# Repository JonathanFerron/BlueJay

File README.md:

# BlueJay
 Split Ergonomic Keyboard

This is a project for a new split ergonomic QMK-powered keyboard. The goal is for it to be minimalist, meant for users who strictly touch-type, and made with easy to solder through-hole components. It is significantly inspired on the [Torn](https://github.com/rtitmuss/torn) split keyboard, with modifications such as adding a partial "numrow" and moving the thumb cluster further out.

This work is licensed under a
[Creative Commons Attribution-NonCommercial-ShareAlike 4.0 International License][cc-by-nc-sa].

[![CC BY-NC-SA 4.0][cc-by-nc-sa-image]][cc-by-nc-sa]

[cc-by-nc-sa]: http://creativecommons.org/licenses/by-nc-sa/4.0/
[cc-by-nc-sa-image]: https://licensebuttons.net/l/by-nc-sa/4.0/88x31.png
[cc-by-nc-sa-shield]: https://img.shields.io/badge/License-CC%20BY--NC--SA%204.0-lightgrey.svg

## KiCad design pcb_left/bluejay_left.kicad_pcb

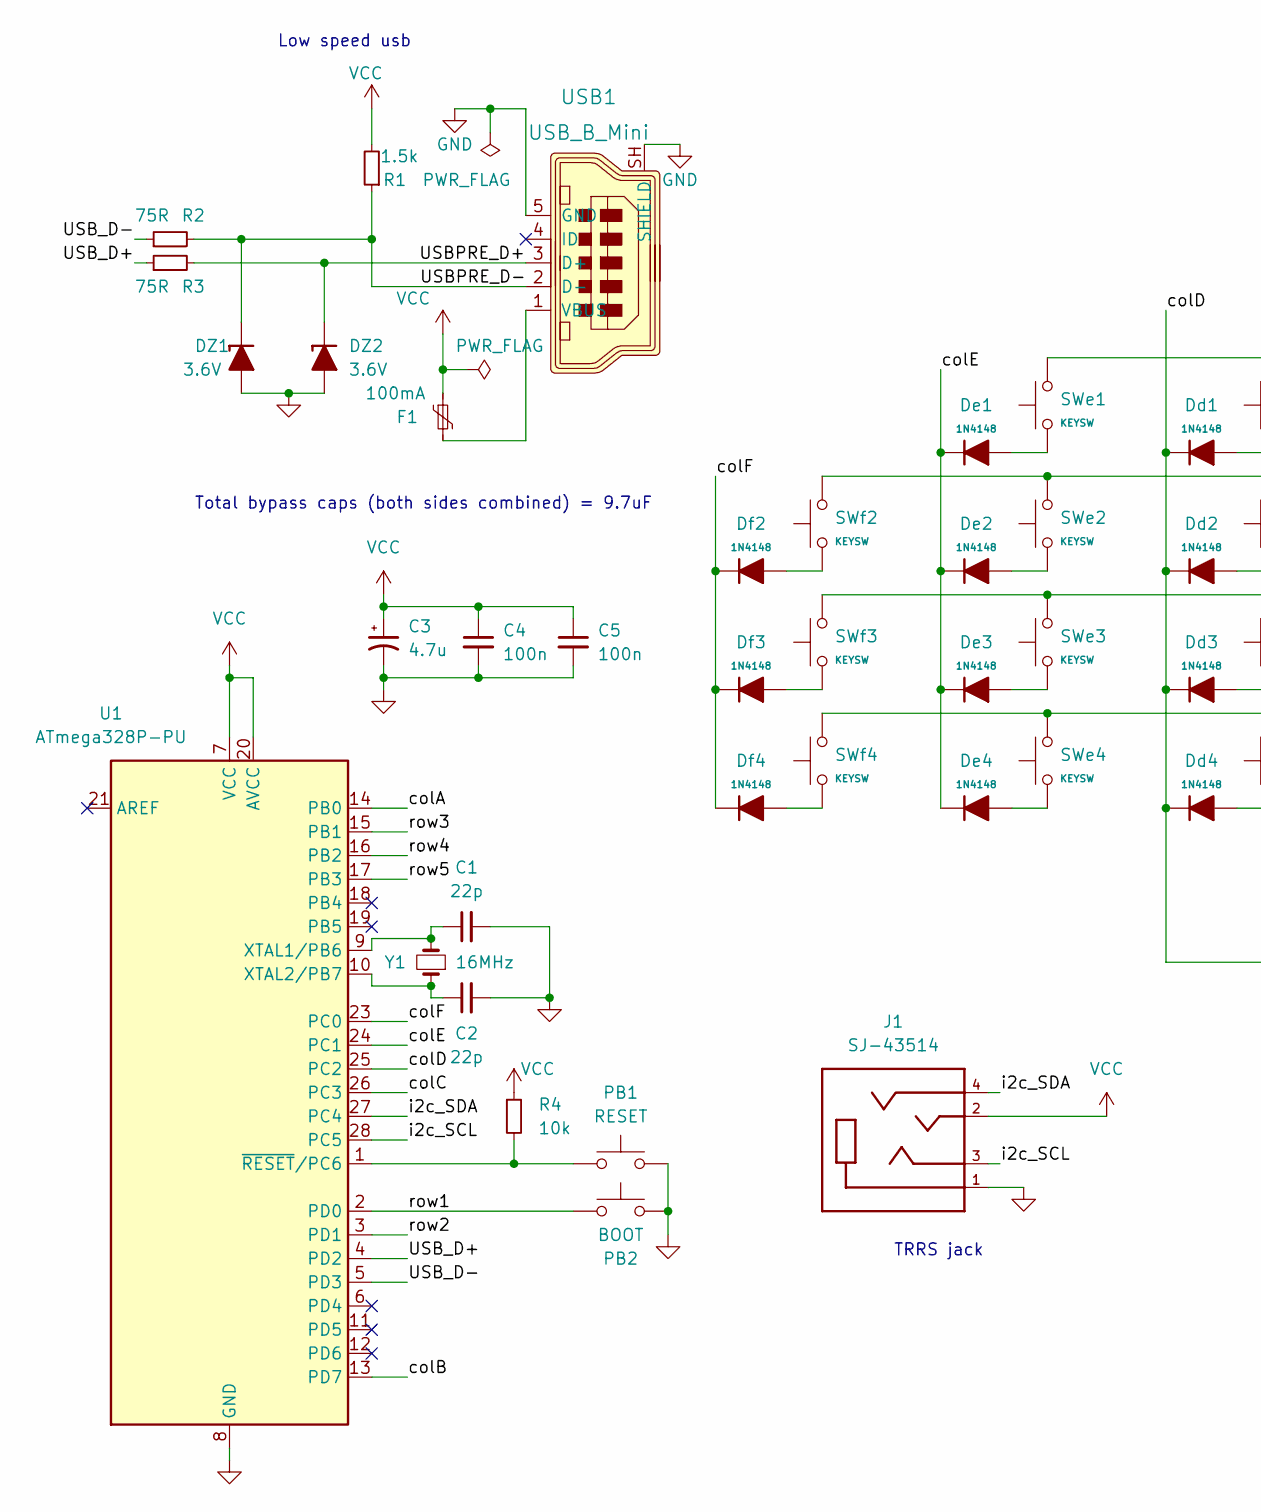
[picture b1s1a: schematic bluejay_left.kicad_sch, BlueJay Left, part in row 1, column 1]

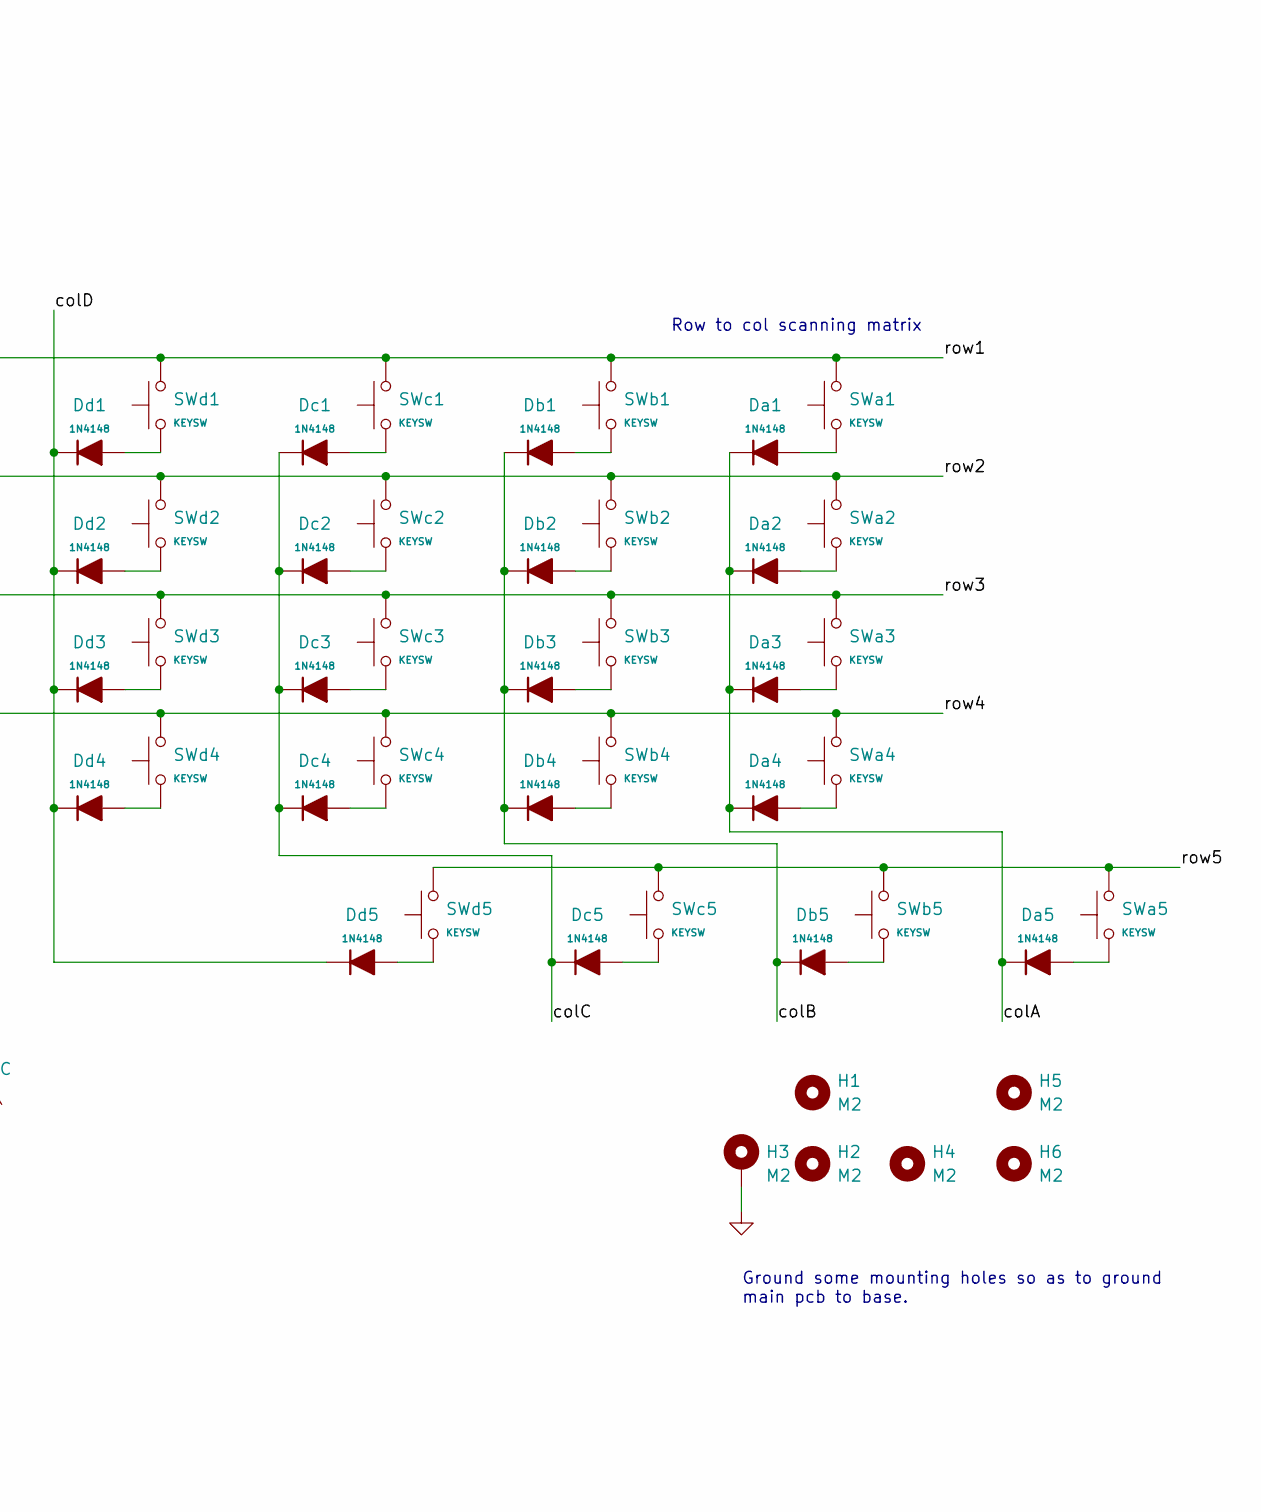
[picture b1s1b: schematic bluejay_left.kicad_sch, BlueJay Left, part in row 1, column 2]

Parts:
C1, C2: 22p; C_Disc_D3.0mm_W1.6mm_P2.50mm
C3: 4.7u; CP_Radial_D4.0mm_P1.50mm
C4, C5: 100n; C_Disc_D4.3mm_W1.9mm_P5.00mm
DZ1, DZ2: 3.6V; D_DO-35_SOD27_P5.08mm_Horizontal
Da1, Da2, Da3, Da4, Da5: 1N4148; D_DO-35_SOD27_P5.08mm_Horizontal
Db1, Db2, Db3, Db4, Db5: 1N4148; D_DO-35_SOD27_P5.08mm_Horizontal
Dc1, Dc2, Dc3, Dc4, Dc5: 1N4148; D_DO-35_SOD27_P5.08mm_Horizontal
Dd1, Dd2, Dd3, Dd4, Dd5: 1N4148; D_DO-35_SOD27_P5.08mm_Horizontal
De1, De2, De3, De4: 1N4148; D_DO-35_SOD27_P5.08mm_Horizontal
Df2, Df3, Df4: 1N4148; D_DO-35_SOD27_P5.08mm_Horizontal
F1: 100mA; polyfuse_5.1mm
H1, H2, H3, H4, H5, H6: M2; MountingHole_2.2mm_M2_Pad
J1: SJ-43514; CUI_SJ-43514; PART_REV 1.04
PB1: RESET; SW_PUSH_6mm
PB2: BOOT; SW_PUSH_6mm
R1: 1.5k; R_Axial_DIN0204_L3.6mm_D1.6mm_P5.08mm_Horizontal
R2, R3: 75R; R_Axial_DIN0204_L3.6mm_D1.6mm_P5.08mm_Horizontal
R4: 10k; R_Axial_DIN0204_L3.6mm_D1.6mm_P5.08mm_Horizontal
SWa1, SWa2, SWa3, SWa4, SWa5: KEYSW; SW_Cherry_MX_PCB_1.00u
SWb1, SWb2, SWb3, SWb4, SWb5: KEYSW; SW_Cherry_MX_PCB_1.00u
SWc1, SWc2, SWc3, SWc4, SWc5: KEYSW; SW_Cherry_MX_PCB_1.00u
SWd1, SWd2, SWd3, SWd4, SWd5: KEYSW; SW_Cherry_MX_PCB_1.00u
SWe1, SWe2, SWe3, SWe4: KEYSW; SW_Cherry_MX_PCB_1.00u
SWf2, SWf3, SWf4: KEYSW; SW_Cherry_MX_PCB_1.00u
U1: ATmega328P-PU; DIP-28_W7.62mm_Socket
USB1: USB_B_Mini; USB_Mini_B_Female_548190519; MPN 0548190519; Digi-Key_PN WM17115-ND
Y1: 16MHz; Crystal_HC49-4H_Vertical

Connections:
/USBPRE_D+: DZ2.1 (K), R3.2, USB1.3 (D+)
/USBPRE_D-: DZ1.1 (K), R1.1, R2.2, USB1.2 (D-)
/USB_D+: R3.1, U1.4 (PD2)
/USB_D-: R2.1, U1.5 (PD3)
/colA: Da1.1 (K), Da2.1 (K), Da3.1 (K), Da4.1 (K), Da5.1 (K), U1.14 (PB0)
/colB: Db1.1 (K), Db2.1 (K), Db3.1 (K), Db4.1 (K), Db5.1 (K), U1.13 (PD7)
/colC: Dc1.1 (K), Dc2.1 (K), Dc3.1 (K), Dc4.1 (K), Dc5.1 (K), U1.26 (PC3)
/colD: Dd1.1 (K), Dd2.1 (K), Dd3.1 (K), Dd4.1 (K), Dd5.1 (K), U1.25 (PC2)
/colE: De1.1 (K), De2.1 (K), De3.1 (K), De4.1 (K), U1.24 (PC1)
/colF: Df2.1 (K), Df3.1 (K), Df4.1 (K), U1.23 (PC0)
/i2c_SCL: J1.3, U1.28 (PC5)
/i2c_SDA: J1.4, U1.27 (PC4)
/row1: PB2.1, SWa1.2, SWb1.2, SWc1.2, SWd1.2, SWe1.2, U1.2 (PD0)
/row2: SWa2.2, SWb2.2, SWc2.2, SWd2.2, SWe2.2, SWf2.2, U1.3 (PD1)
/row3: SWa3.2, SWb3.2, SWc3.2, SWd3.2, SWe3.2, SWf3.2, U1.15 (PB1)
/row4: SWa4.2, SWb4.2, SWc4.2, SWd4.2, SWe4.2, SWf4.2, U1.16 (PB2)
/row5: SWa5.2, SWb5.2, SWc5.2, SWd5.2, U1.17 (PB3)
GND: C1.2, C2.2, C3.2, C4.2, C5.2, DZ1.2 (A), DZ2.2 (A), H3.1, J1.1, PB1.2, PB2.2, U1.8 (GND), U1.22 (GND), USB1.5 (GND), USB1.SH (SHIELD)
unnamed: C1.1, U1.9 (XTAL1/PB6), Y1.2
unnamed: C2.1, U1.10 (XTAL2/PB7), Y1.1
unnamed: Da1.2 (A), SWa1.1
unnamed: Da2.2 (A), SWa2.1
unnamed: Da3.2 (A), SWa3.1
unnamed: Da4.2 (A), SWa4.1
unnamed: Da5.2 (A), SWa5.1
unnamed: Db1.2 (A), SWb1.1
unnamed: Db2.2 (A), SWb2.1
unnamed: Db3.2 (A), SWb3.1
unnamed: Db4.2 (A), SWb4.1
unnamed: Db5.2 (A), SWb5.1
unnamed: Dc1.2 (A), SWc1.1
unnamed: Dc2.2 (A), SWc2.1
unnamed: Dc3.2 (A), SWc3.1
unnamed: Dc4.2 (A), SWc4.1
unnamed: Dc5.2 (A), SWc5.1
unnamed: Dd1.2 (A), SWd1.1
unnamed: Dd2.2 (A), SWd2.1
unnamed: Dd3.2 (A), SWd3.1
unnamed: Dd4.2 (A), SWd4.1
unnamed: Dd5.2 (A), SWd5.1
unnamed: De1.2 (A), SWe1.1
unnamed: De2.2 (A), SWe2.1
unnamed: De3.2 (A), SWe3.1
unnamed: De4.2 (A), SWe4.1
unnamed: Df2.2 (A), SWf2.1
unnamed: Df3.2 (A), SWf3.1
unnamed: Df4.2 (A), SWf4.1
unnamed: F1.2, USB1.1 (VBUS)
unnamed: PB1.1, R4.2, U1.1 (~RESET/PC6)
VCC: C3.1, C4.1, C5.1, F1.1, J1.2, R1.2, R4.1, U1.7 (VCC), U1.20 (AVCC)

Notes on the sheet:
Low speed usb
Total bypass caps (both sides combined) = 9.7uF
TRRS jack
Row to col scanning matrix
Ground some mounting holes so as to ground main pcb to base.

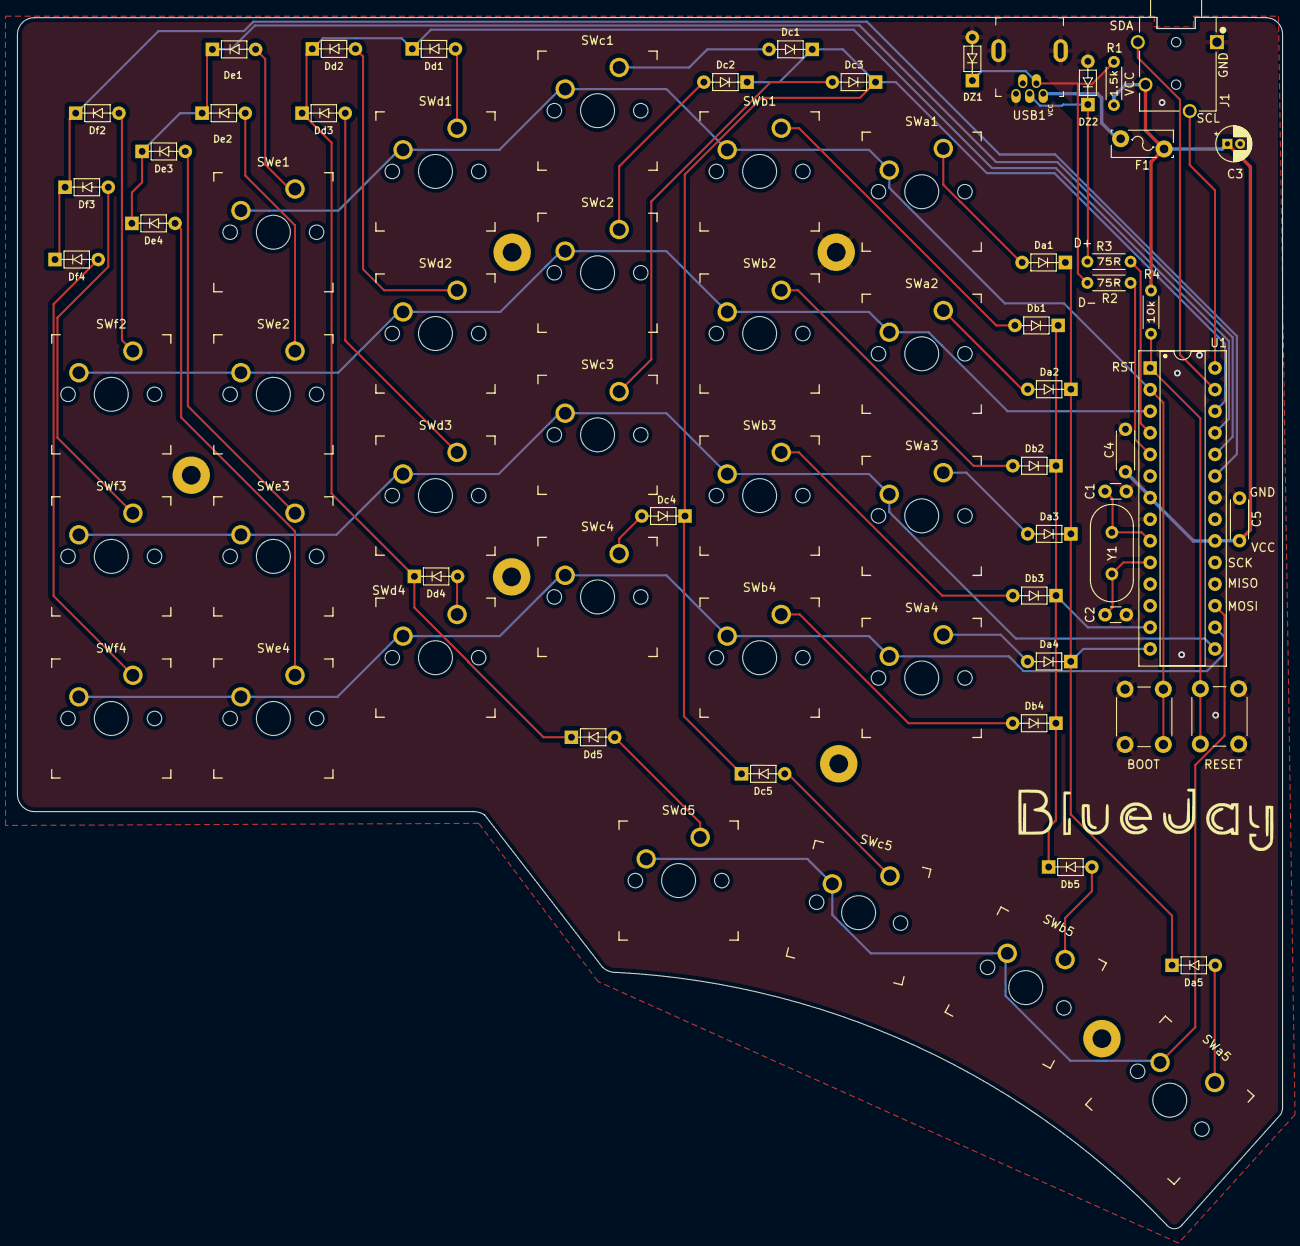
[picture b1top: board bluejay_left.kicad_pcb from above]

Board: 2 copper layers, 148.7 x 142.4 mm, 79 parts (0 on the bottom side), 50 nets.

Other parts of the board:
Ref**: Val**; BlueJay in Halfomania font

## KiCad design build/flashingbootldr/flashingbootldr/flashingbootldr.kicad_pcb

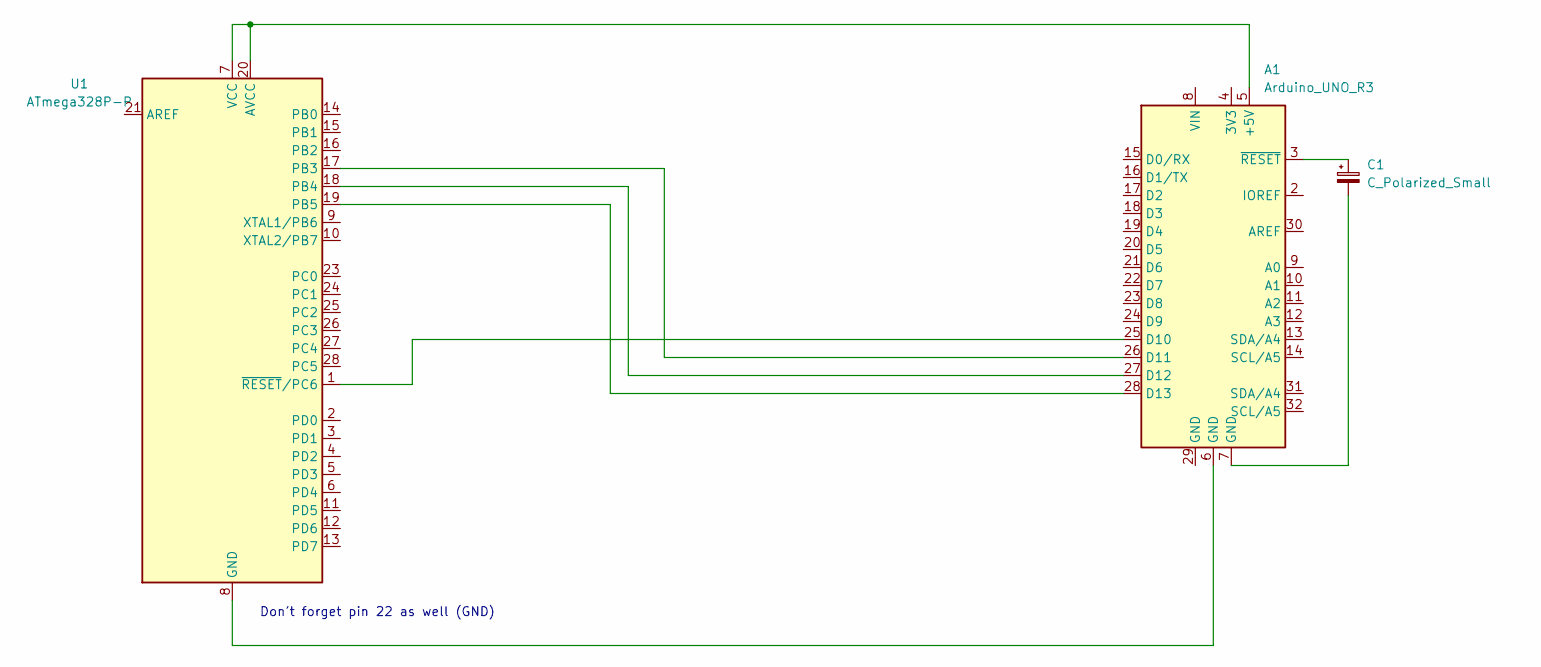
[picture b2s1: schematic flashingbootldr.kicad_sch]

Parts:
A1: Arduino_UNO_R3
C1: C_Polarized_Small; CP_Radial_D5.0mm_P2.50mm
U1: ATmega328P-P; DIP-28_W7.62mm

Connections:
unnamed: A1.3 (~RESET), C1.1
unnamed: A1.7 (GND), C1.2
unnamed: A1.26 (D11), U1.17 (PB3)
unnamed: A1.25 (D10), U1.1 (~RESET/PC6)
unnamed: A1.27 (D12), U1.18 (PB4)
unnamed: A1.28 (D13), U1.19 (PB5)
unnamed: A1.5 (+5V), U1.7 (VCC), U1.20 (AVCC)
unnamed: A1.6 (GND), U1.8 (GND), U1.22 (GND)

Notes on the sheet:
Don't forget pin 22 as well (GND)

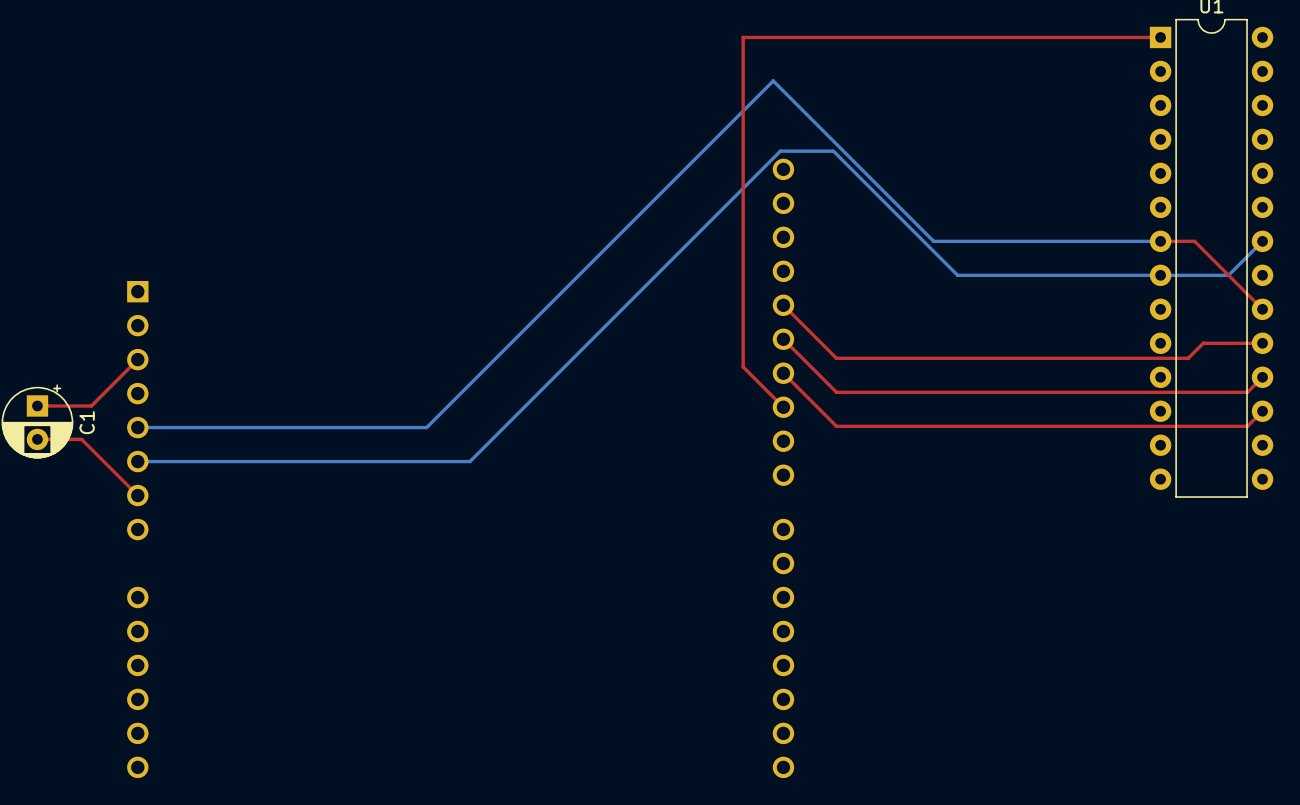
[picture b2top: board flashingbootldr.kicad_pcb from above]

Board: 2 copper layers, 3 parts (1 on the bottom side), 8 nets.

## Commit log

2022-06-08 Initial commit for basic design files.
2022-06-08 Initial commit - folder structure for project
2022-06-09 More early design files
2022-06-09 ATMega datasheet
2022-06-15 Prep work to start PCB design
2022-06-17 Some prep work done for PCB
2022-06-17 Update documentation on MCUs
2022-06-17 Start building left pcb
2022-06-18 More work on left hand schematic
2022-06-18 Rename LICENSE.md to LICENSE
2022-06-18 Add license
2022-06-18 Further progress with left hand schematic
2022-06-19 Complete left hand schematic
2022-06-19 Complete right hand schematic
2022-06-20 Further work on schematics
2022-06-20 More work on schematics
2022-06-20 Some updates to schematics before moving to pcb design
2022-06-21 Work on PCBs
2022-06-21 Further work on pcbs
2022-06-22 Further PCB updates
2022-06-28 Preliminary routing left hand pcb
2022-06-28 Update documentation
2022-06-28 Tweaks to component placements - left hand
2022-06-28 Further updates to pcb
2022-06-29 Updates to pcb design rules
2022-06-30 Tweak USB data lines
2022-06-30 Begin work on right pcb
2022-07-01 Routing of right PCB
2022-07-02 Fine tune placement of switches - right hand
2022-07-03 Fine tune alignment of diodes and resistors
2022-07-03 Update documentation
2022-07-03 No need for decoupling cap on reset pin
2022-07-03 Update doc
2022-07-04 Add mounting holes
2022-07-06 Tweak placement of components on left hand
2022-07-10 Finish aligning switches, start work on plate
2022-07-12 Start work on plate
2022-07-12 Ground a couple mounting holes so as to ground plate and base too
2022-07-12 work on plate
2022-07-16 Test alternative component placement to see what happens
2022-07-18 Alternative approach to place diodes
2022-07-19 Fine tune placement of diodes
2022-07-20 Complete alternative version of pcbs
2022-07-21 Create base pcb
2022-07-22 add logo
2022-07-24 Fine tune pcbs
2022-07-26 Produce test gerber files
2022-07-28 Update schematics in preparation for review
2022-07-30 Fine tuning of schematics and pcbs in prep for review
2022-08-02 Update logo
2022-08-04 Produce some printouts for review
2022-08-04 Instructions on how to flash bootloader
2022-08-07 Diagram for flashing of bootloader
2022-08-14 remove mounting hole 9
2022-08-15 Round edges of PCB
2022-08-25 tweak board edges
2022-09-01 fine tune edge cuts
2022-09-04 Fine tuning of edge cut for plate
2022-09-08 Few updates to to dos
2022-09-10 Update placement of some components and size of drill holes
2022-09-13 update bootloader flashing instructions
2022-09-14 Fine tune edge cut
2022-09-14 Further work on plate
2022-09-26 Add some info for breadboarding model
2022-10-14 Update gerber files
2022-10-17 simple corrections in prep for rev 1.1
2022-11-17 A few simple tweaks
2023-06-16 fix routing with usb connector
